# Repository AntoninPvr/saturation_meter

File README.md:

# Saturation meter

A simple saturation meter to estimate the saturation current of inductors.

This project is a quick and dirty implementation, and is not intended for production use. I need to measure the saturation current of some inductors for a project, so I built this tool to help me do that.

I used only parts I had lying around, and I want to use isolation milling, so the design is not optimal.

## Assembly

## 3D Model

To protect the circuit, I designed a simple enclosure that can be 3D printed. and laser cut.

All files are in the `cad` folder.

- [bottom.stl](cad/bottom.stl)

- [sides.stl](cad/sides.stl)

- [top.svg](cad/top.svg) (for laser cutting red 0.2mm stroke)

## Design

It is based on a discussion on the EEVblog forum: https://www.eevblog.com/forum/beginners/help-with-testing-inductor-saturation-current/
The idea is to discharge a capacitor through the inductor and measure the voltage and current across the inductor. When the inductor saturates, the dI/dt increases, (ie L decreases).

To measure the voltage and current, I use a STM32F103 with its built-in ADC. I choose to not use any op-amps to keep the design simple.

### MOSFETs

I use two N-channel MOSFETs (BUK556), they are driven by the IR2112, but not in the usual half-bridge configuration.

The low-side MOSFET (Q2) is ON before the high-side MOSFET (Q1) in order to charge the bootstrap capacitor (C12). Then Q1 is turned ON to let current flow through the inductor under test.

Almost any N-channel MOSFET with a Vds rating of at least 30V and a low Rds(on) will work. For the bootstrap capacitor (C12), I recommend at least 1uF. Because the ON time of Q1 is relatively long compared to a typical half-bridge application, a larger capacitor will help maintain the gate voltage.

### Current sensing

I don't have a proper shunt resistor, so I made a shunt using PCB traces. The shunt resistor (R9) is designed to have a resistance of **60mΩ with a 1oz** PCB. Keep in mind that the copper thermal coefficient of resistance is poor, so the resistance will vary with temperature. But because the current is measured over a short period of time, the temperature rise should be minimal.

You will need to calibrate the shunt resistor by measuring the voltage drop across it at a known current, because the actual resistance may vary due to manufacturing tolerances (especially with isolation milling).

### LEDs

Two LEDs give visual feedback about the operation of the circuit:

- D5 (green): indicates that the circuit is powered.
- D6 (yellow): inidicates that the capacitor bank is being charged.

## Schematic

## Layout

The layout is designed for isolation milling. It complies with the following rules:

- Minimum trace width: 0.2mm (recommended: 0.3mm)
- Minimum clearance: 0.3mm
- No plated through holes

I choose a **single layer design** to keep it simple, therefore traces routed on the top layer are straps. Nevertheless, I added front copper plane because the LPKG S63 I use is able to do double layer PCB. Because I cant do vias, I had to add some **jumpers to connect the top and bottom layers**.

## BOM

Use the [interactive BOM viewer](ibom.html)

| Reference | Qty | Value | Footprint |
|----------|-----|-------|-----------|
| C1,C2,C3,C4 | 4 | 4700u | Capacitor_THT:CP_Radial_D30.0mm_P10.00mm_SnapIn |
| C5,C6,C7,C10 | 4 | 1n | Capacitor_THT:C_Disc_D6.0mm_W2.5mm_P5.00mm |
| C8,C11 | 2 | 100n | Capacitor_THT:C_Disc_D6.0mm_W2.5mm_P5.00mm |
| C9,C12,C13 | 3 | 2u2 | Capacitor_THT:CP_Radial_D6.3mm_P2.50mm |
| D1,D2,D3 | 3 | 1N5822 | Diode_THT:D_DO-201AD_P15.24mm_Horizontal |
| D4,D7 | 2 | 1N4007 | Diode_THT:D_DO-41_SOD81_P10.16mm_Horizontal |
| D5,D6 | 2 | LED | LED_THT:LED_D5.0mm |
| H1,H2,H3,H4,H5 | 5 | MountingHole | MountingHole:MountingHole_3.2mm_M3_DIN965 |
| J1 | 1 | Vin | TerminalBlock:TerminalBlock_MaiXu_MX126-5.0-02P_1x02_P5.00mm |
| J2 | 1 | DUT | Connector:Banana_Jack_2Pin |
| J3 | 1 | Inputs | Connector_PinHeader_2.54mm:PinHeader_1x03_P2.54mm_Vertical |
| J4 | 1 | Outputs | Connector_PinHeader_2.54mm:PinHeader_1x04_P2.54mm_Vertical |
| J5 | 1 | UC | Connector_PinHeader_2.54mm:PinHeader_1x02_P2.54mm_Vertical |
| Q1,Q2 | 2 | BUK556 | Package_TO_SOT_THT:TO-220-3_Vertical |
| Q4 | 1 | BC638 | Package_TO_SOT_THT:TO-92_Inline |
| R1 | 1 | 10 | Resistor_THT:R_Axial_DIN0617_L17.0mm_D6.0mm_P20.32mm_Horizontal |
| R2,R7,R13,R15,R16 | 5 | 100 | Resistor_THT:R_Axial_DIN0207_L6.3mm_D2.5mm_P10.16mm_Horizontal |
| R3,R4,R12,R17,R18,R19,R20 | 7 | 8k2 | Resistor_THT:R_Axial_DIN0207_L6.3mm_D2.5mm_P10.16mm_Horizontal |
| R5,R6,R11,R14 | 4 | 1k6 | Resistor_THT:R_Axial_DIN0207_L6.3mm_D2.5mm_P10.16mm_Horizontal |
| R8,R10 | 2 | 1k | Resistor_THT:R_Axial_DIN0207_L6.3mm_D2.5mm_P10.16mm_Horizontal |
| R9 | 1 | 60m | shunt:R_Shunt_kelvin_60mohm |
| U1 | 1 | LF33_TO220 | Package_TO_SOT_THT:TO-220-3_Vertical |
| U2 | 1 | IR2112 | Package_DIP:DIP-14_W7.62mm |

## Firmware

The firmware is available on its dedicated repository: https://github.com/AntoninPvr/saturation_meter_firmware

## ToDo

- [ ] Add test results

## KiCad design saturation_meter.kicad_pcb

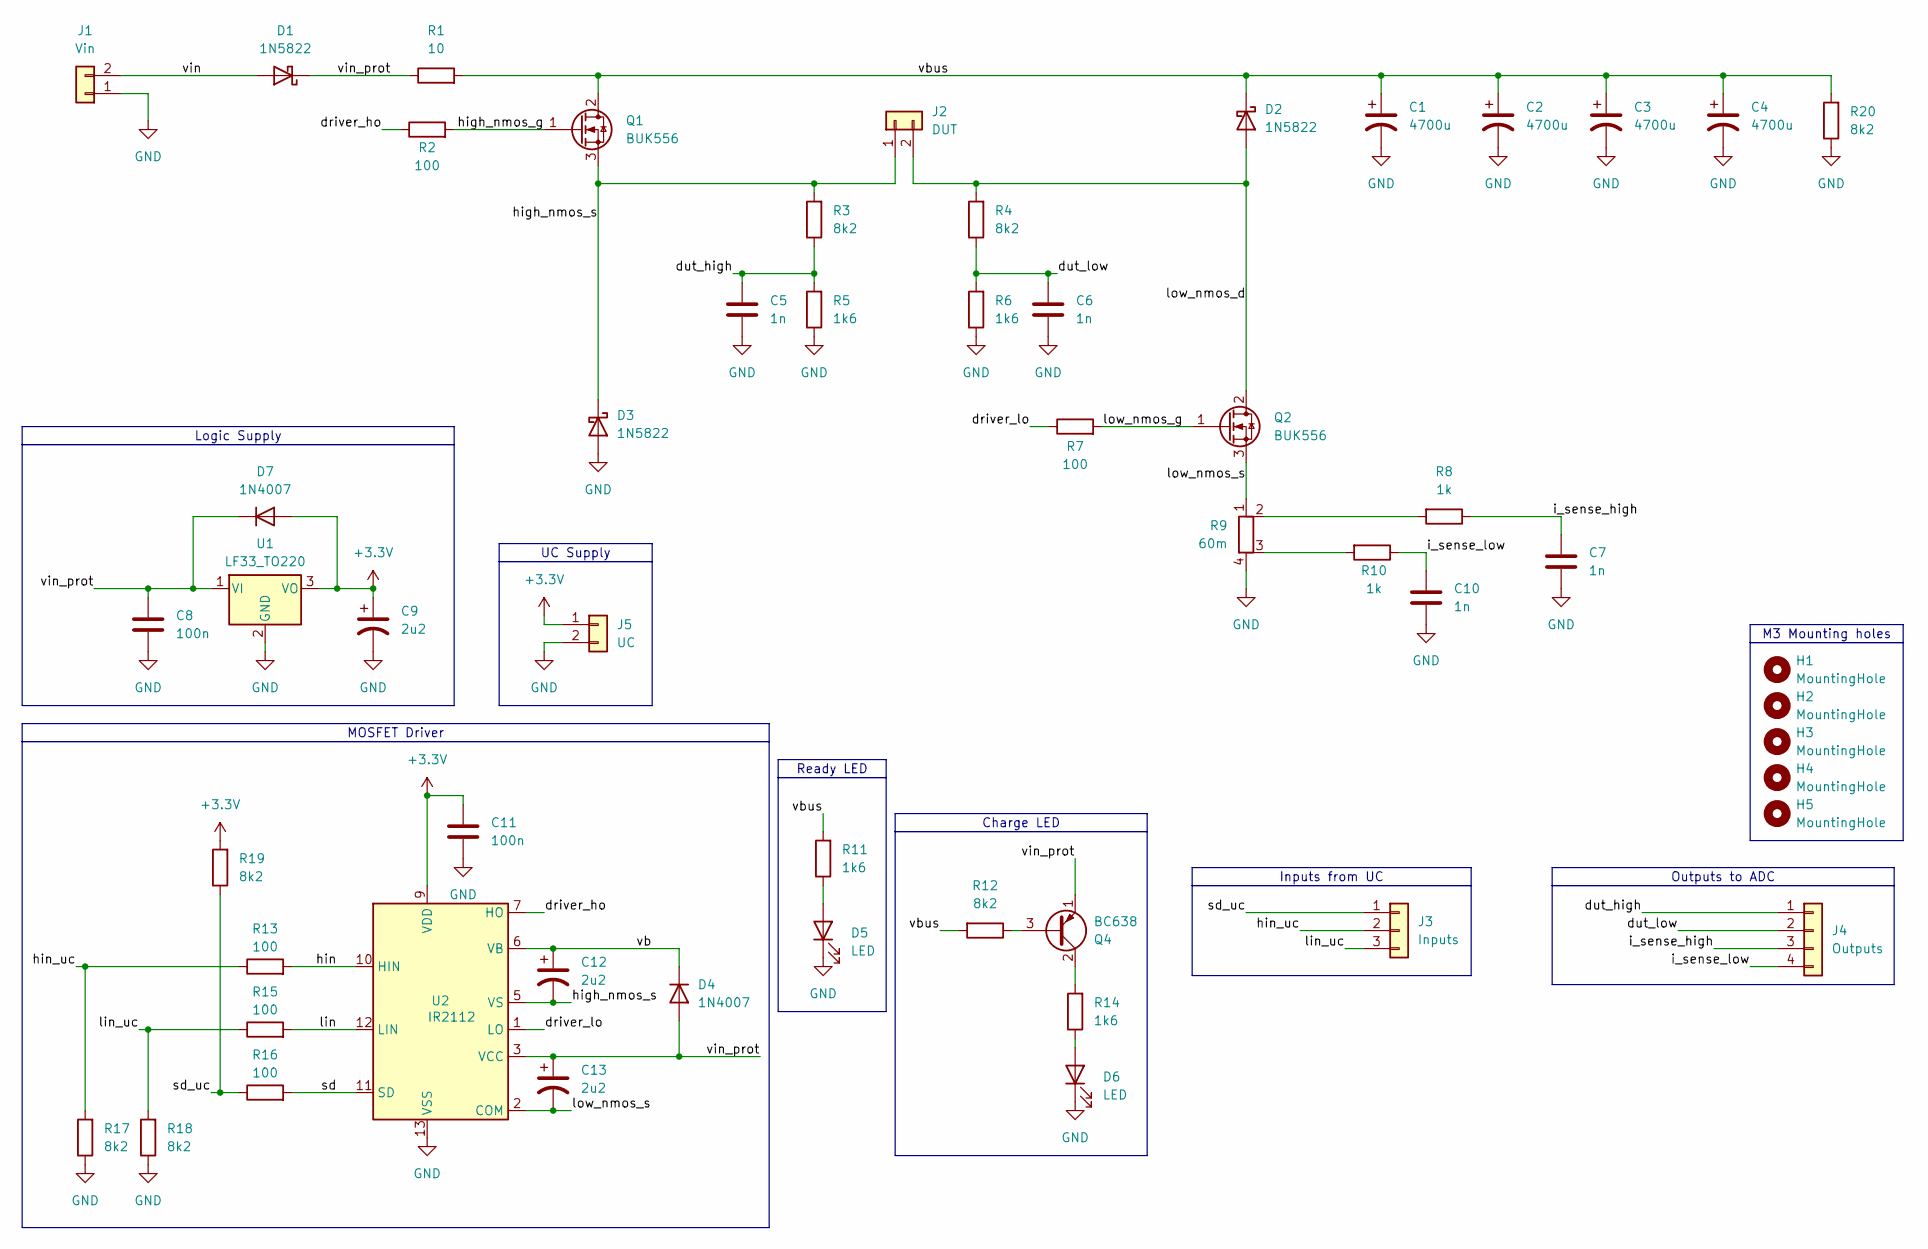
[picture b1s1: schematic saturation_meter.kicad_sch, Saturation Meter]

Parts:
C1, C2, C3, C4: 4700u; CP_Radial_D30.0mm_P10.00mm_SnapIn
C5, C6, C7, C10: 1n; C_Disc_D6.0mm_W2.5mm_P5.00mm
C8, C11: 100n; C_Disc_D6.0mm_W2.5mm_P5.00mm
C9, C12, C13: 2u2; CP_Radial_D6.3mm_P2.50mm
D1, D2, D3: 1N5822; D_DO-201AD_P15.24mm_Horizontal
D4, D7: 1N4007; D_DO-41_SOD81_P10.16mm_Horizontal
D5, D6: LED; LED_D5.0mm
H1, H2, H3, H4, H5: MountingHole; MountingHole_3.2mm_M3_DIN965
J1: Vin; TerminalBlock_MaiXu_MX126-5.0-02P_1x02_P5.00mm
J2: DUT; Banana_Jack_2Pin
J3: Inputs; PinHeader_1x03_P2.54mm_Vertical
J4: Outputs; PinHeader_1x04_P2.54mm_Vertical
J5: UC; PinHeader_1x02_P2.54mm_Vertical
Q1, Q2: BUK556; TO-220-3_Vertical
Q4: BC638; TO-92_Inline
R1: 10; R_Axial_DIN0617_L17.0mm_D6.0mm_P20.32mm_Horizontal
R2, R7, R13, R15, R16: 100; R_Axial_DIN0207_L6.3mm_D2.5mm_P10.16mm_Horizontal
R3, R4, R12, R17, R18, R19, R20: 8k2; R_Axial_DIN0207_L6.3mm_D2.5mm_P10.16mm_Horizontal
R5, R6, R11, R14: 1k6; R_Axial_DIN0207_L6.3mm_D2.5mm_P10.16mm_Horizontal
R8, R10: 1k; R_Axial_DIN0207_L6.3mm_D2.5mm_P10.16mm_Horizontal
R9: 60m; R_Shunt_kelvin_60mohm
U1: LF33_TO220; TO-220-3_Vertical
U2: IR2112; DIP-14_W7.62mm

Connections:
+3.3V: C9.1, C11.1, D7.2 (A), J5.1, R19.2, U1.3 (VO), U2.9 (VDD)
/driver_ho: R2.1, U2.7 (HO)
/driver_lo: R7.1, U2.1 (LO)
/dut_high: C5.1, J4.1, R3.1, R5.2
/dut_low: C6.1, J4.2, R4.1, R6.2
/high_nmos_g: Q1.1 (G), R2.2
/high_nmos_s: C12.2, D3.1 (K), J2.1, Q1.3 (S), R3.2, U2.5 (VS)
/hin: R13.2, U2.10 (HIN)
/hin_uc: J3.2, R13.1, R17.2
/i_sense_high: C7.1, J4.3, R8.1
/i_sense_low: C10.1, J4.4, R10.1
/lin: R15.2, U2.12 (LIN)
/lin_uc: J3.3, R15.1, R18.2
/low_nmos_d: D2.2 (A), J2.2, Q2.2 (D), R4.2
/low_nmos_g: Q2.1 (G), R7.2
/low_nmos_s: C13.2, Q2.3 (S), R9.1, U2.2 (COM)
/sd: R16.2, U2.11 (SD)
/sd_uc: J3.1, R16.1, R19.1
/vb: C12.1, D4.1 (K), U2.6 (VB)
/vbus: C1.1, C2.1, C3.1, C4.1, D2.1 (K), Q1.2 (D), R1.2, R11.2, R12.2, R20.2
/vin: D1.2 (A), J1.2
/vin_prot: C8.1, C13.1, D1.1 (K), D4.2 (A), D7.1 (K), Q4.1 (E), R1.1, U1.1 (VI), U2.3 (VCC)
GND: C1.2, C2.2, C3.2, C4.2, C5.2, C6.2, C7.2, C8.2, C9.2, C10.2, C11.2, D3.2 (A), D5.1 (K), D6.1 (K), J1.1, J5.2, R5.1, R6.1, R9.4, R17.1, R18.1, R20.1, U1.2 (GND), U2.13 (VSS)
unnamed: D5.2 (A), R11.1
unnamed: D6.2 (A), R14.1
unnamed: Q4.3 (B), R12.1
unnamed: Q4.2 (C), R14.2
unnamed: R8.2, R9.2
unnamed: R9.3, R10.2

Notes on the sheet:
Ready LED
UC Supply
M3 Mounting holes
Charge LED
Logic Supply
Inputs from UC
Outputs to ADC
MOSFET Driver

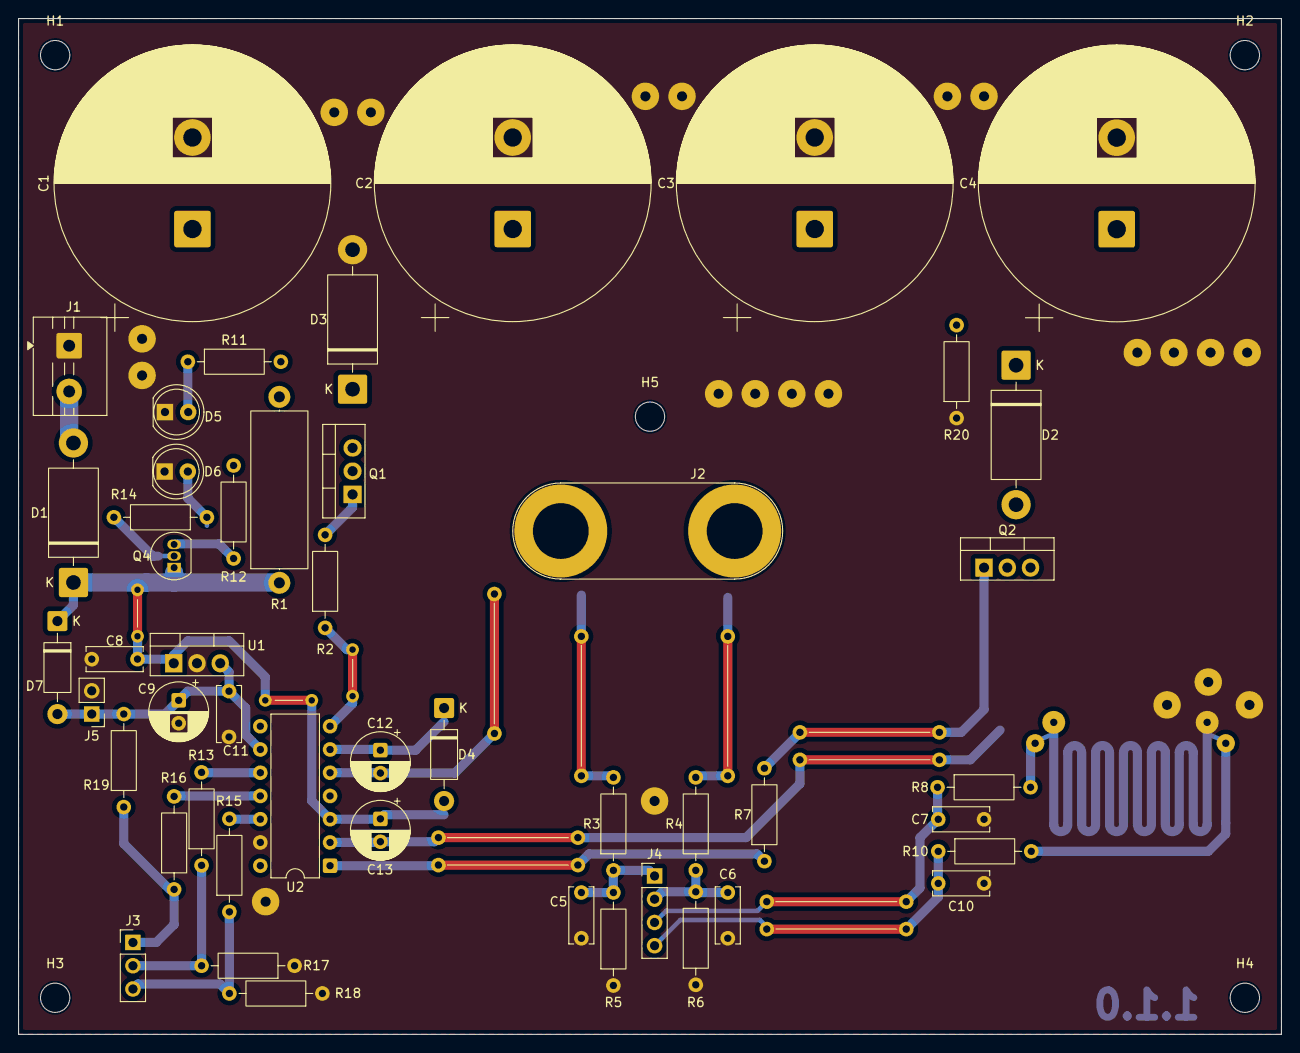
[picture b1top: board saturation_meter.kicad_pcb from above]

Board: 2 copper layers, 138.0 x 111.0 mm, 55 parts (0 on the bottom side), 29 nets.

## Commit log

2025-12-09 Added cap
2025-12-09 Released 1.0.0 of schematic
2025-12-10 First version of PCB, ready to isolation milling
2025-12-10 Added version number
2025-12-10 Added schematic.pdf and readme
2025-12-10 Added pictures and updated design sheet
2025-12-11 Added production files for back layer
2025-12-11 Updated to double layer
2025-12-14 Updated to v1.1.0 fixed, shutdown of ir2112, added enclosure
2025-12-14 Remove useless img
2025-12-16 Added BOM.csv
2025-12-16 Added firmware link in readme
